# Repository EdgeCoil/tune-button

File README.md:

# Tune Button

A pocket remote for Spotify on Android. Out of the box its four keys **like** the song that's
playing, **add it to a playlist**, **skip**, and **play or pause**. Each key can also do something
else when held or double-pressed. It runs for months on a small battery and charges over USB-C.

It is **not a Bluetooth keyboard**, so nothing on the phone gets remapped. Each press sends a small,
signed Bluetooth broadcast. A companion app hears it in the background, even with the phone locked,
and does what you set that key to do.

<sub>The three four-key boards (renders of rev A, which has arrived and is being brought up): `c3-jst` with buttons on a cable, the XIAO board, and the C3 board's key side.</sub>

```
 button ──wake──► ESP32-C3 ──signed BLE broadcast──► Android app ──HTTPS──► Spotify
                 (deep sleep)                      (listens in the         like, add, skip,
                                                    background)            play/pause, …
```

> **Status: works end to end.** A one-button unit on a XIAO ESP32-C3 liked the playing song from a
> locked Samsung phone; the app heard the press in 0.8 s. The four-key firmware and app (holds,
> double presses, playback control) are written and unit-tested; on the rev A boards the C3 board's
> four keys, sleep and wake work (2026-11-05), the XIAO board is flashed (without a cell so far), and the app hasn't been
> paired with a four-key board yet. Still to do: a longer latency run on each scan mode and a
> battery-life measurement. See [`docs/design.md`](docs/design.md).

## What you need

- **The button:** one of the four-key boards (see [Hardware](#hardware)), or a hand-wired Seeed
  Studio XIAO ESP32-C3 with a small LiPo cell and one or two 12 mm tactile switches
  ([`hardware/wiring.md`](hardware/wiring.md)). There are 3D-printable cases, and layered acrylic
  cases for the four-key boards ([`hardware/case`](hardware/case/README.md)).
- **An Android phone**, version 8.0 or later.
- **Spotify Premium.** Spotify requires it on the account that owns the developer app, and the
  developer app works for up to five users.

## Set up

### 1. Create a Spotify developer app

1. Sign in at [developer.spotify.com/dashboard](https://developer.spotify.com/dashboard) and create
   an app. Tick **Web API**.
2. Add the redirect URI **`tunebutton://callback`**.
3. Copy the **Client ID**. You don't need a client secret: the app signs in with PKCE.

### 2. Flash the firmware

Pick the build for your button:

| Button | Build (`-e`) | `sh scripts/merge.sh <build>` makes |
|---|---|---|
| Hand-wired XIAO, two buttons | `xiao_esp32c3` (the default) | `tune-button-c3.bin` |
| Hand-wired XIAO, one button | `xiao_esp32c3_1btn` | `tune-button-c3-1btn.bin` |
| XIAO four-key board | `xiao_board` | `tune-button-xiao-board.bin` |
| `c3` or `c3-jst` board | `c3_board` | `tune-button-c3-board.bin` |

With PlatformIO:

```bash
cd firmware
pio test -e native            # host tests: packet encoder, signatures and key gestures
pio run -e c3_board -t upload # build and flash over USB-C
```

Or make one image (table above) and flash it at offset `0x0`, either in Chrome with
[esptool-js](https://espressif.github.io/esptool-js/) or with
`esptool.py --chip esp32c3 write_flash 0 tune-button-c3.bin`.

**Only have one button?** Wire it to D1. A press acts when you let go; holding it for 5 seconds pairs.

Things worth knowing:
- **On a computer's USB it stays awake**, so the serial port stays up: `pio device monitor` shows a
  line per wake and per key sent, and `pio run -t upload` works as is. It notices within a few ms
  when the computer goes away, and sleeps. A plain USB charger sends no USB frames, so on one it
  sleeps as usual. Build with `-DTB_USB_HEARTBEAT` to also print the raw key state once a second.
- **Otherwise the USB port vanishes while the button sleeps**, which is almost all the time. To
  flash it, plug it into a computer and press a key (it stays up once the press is sent), or hold
  **BOOT** while plugging it in.
- **If it sits in `waiting for download` after an upload**, the reset after flashing kept it in
  the bootloader: unplug and replug it. `--after watchdog_reset` (esptool) avoids this.
- **Flashing the merged image at `0x0` erases the pairing**, so pair again afterwards.
  `pio run -t upload` keeps it.
- Build options in `platformio.ini`: `TB_BURST_MS` (how long each press is broadcast) and `TB_LED_PIN`.
- **Updating from the two-button firmware** keeps the pairing (with `pio run -t upload`), and the
  app still understands a button that hasn't been updated.

### 3. Install the app

```bash
cd android
./gradlew test assembleDebug      # needs JDK 17+ and Android SDK 35
```

Install `app/build/outputs/apk/debug/app-debug.apk` on the phone, open it and work down the screen:

1. Paste the Client ID and tap **Sign in to Spotify**. (Signed in before playback control existed?
   The app asks you to sign in again, to allow it.)
2. **Pair:** hold keys 1 and 2 (top left and top right) for 3 seconds (one-button build: hold it for
   5 seconds) until the LED flickers, then tap **Pair**. Accept the Bluetooth prompt if one appears.
   Pairing makes a fresh key, so a previously paired phone stops working; a pairing that no phone
   completes changes nothing.
3. **Keys:** tap any key's press, hold or double press to choose what it does. Key 2's press needs
   a playlist.
4. Fix everything listed under *Keep listening in the background*. **On Samsung phones, also add the
   app to *Never sleeping apps*,** or presses stop being heard after a few days.
5. Tap **Test without the device** to check the Spotify side on its own.

## Using it

Press a key. Within a moment the phone buzzes once and shows a notification, for example
"♥ Liked — Title · Artist" or "⏭ Next track". If something goes wrong it buzzes twice and says why:
nothing playing, signed out, a local file, and so on. Podcast episodes work too.

What a key can do, on press, hold (0.6 s) or double press:

| | |
|---|---|
| **The song** | like it, remove it from Liked Songs, add it to a playlist, remove it from a playlist |
| **Playback** | play / pause, next, previous, volume up or down 10 %, shuffle on / off, repeat (off → all → one), play a playlist |
| **Anything else** | call a webhook, such as a Home Assistant automation. It gets the key, the gesture and the song |

Each slot has its own playlist, so key 2 could add to one playlist and key 2 held to another.

**Holds and double presses cost a little speed, on that key only.** A key with nothing on hold or
double press sends the moment it goes down. One with a hold action waits for you to let go (or for
the hold); one with a double press waits 0.3 s for a second press. The button has to know which keys
wait, so after changing those, the app asks you to hold keys 1 and 2 for 3 seconds and tap **Send
key settings**. That doesn't re-pair anything.

Quick presses all count: three fast presses of skip are three skips.

The app's *Recent presses* list shows, for each press, how long the phone took to hear it, how long
Spotify took, the button's battery level and the result.

## Hardware

| Option | What it is | State |
|---|---|---|
| **Hand-wired XIAO** | A XIAO ESP32-C3 with one or two switches and a LiPo: [`hardware/wiring.md`](hardware/wiring.md) | One-button unit built and working |
| **3D-printed case** | Parametric OpenSCAD, with ready STLs: [`hardware/case/`](hardware/case/) | Ready to print |
| **Four-key PCBs** | Three boards: one carrying a XIAO, one with the ESP32-C3 module on board, and a small one that takes buttons on a cable. [`hardware/pcb/`](hardware/pcb/) | Rev A in bring-up; XIAO rev B designed |

The firmware supports all four boards. It runs on the rev A C3 board and is flashed on the rev A XIAO board (without a cell so far); `c3-jst` is untested.

## How it's put together

| Path | What it is |
|---|---|
| [`firmware/`](firmware/) | PlatformIO / Arduino firmware for the ESP32-C3 (NimBLE) |
| [`android/`](android/) | The companion app (Kotlin, Android 8+) |
| [`protocol/`](protocol/) | The broadcast format, and `gen_vectors.py`, which makes the test vectors both sides check against |
| [`hardware/`](hardware/) | Wiring, parts, the case and the PCBs |
| [`docs/design.md`](docs/design.md) | How it works, security, power budget, latency and bench tests |

Each press is signed with a key shared at pairing and carries a counter, so the app ignores copies
and anything not from your button. [`docs/design.md`](docs/design.md) has the details.

## Licence

| What | Licence |
|---|---|
| The case and PCBs: `hardware/case/`, `hardware/pcb/` (OpenSCAD and KiCad sources, STLs) | [CERN-OHL-S-2.0](LICENSES/CERN-OHL-S-2.0.txt) |
| Firmware, app, protocol tools | [MIT](LICENSES/MIT.txt) |
| The Gradle wrapper (`android/gradlew*`, `android/gradle/wrapper/`), as shipped by Gradle | [Apache-2.0](LICENSES/Apache-2.0.txt) |
| Documentation (`README.md`, `docs/` including the renders, `hardware/wiring.md`, `protocol/spec.md`) | [CC BY 4.0](LICENSES/CC-BY-4.0.txt) |
| The EdgeCoil mark (`hardware/pcb/edgecoil-mark.svg` and the silkscreen drawn from it), name and URL | [All rights reserved](LICENSES/LicenseRef-EdgeCoil-Mark.txt) |

Each source file carries an SPDX header, and [`REUSE.toml`](REUSE.toml) covers the rest by path.

The board licence does not cover the EdgeCoil mark, name or URL on the silkscreen. If you make or
sell boards from these designs, take them off.

Spotify is a trademark of Spotify AB. This project is not affiliated with or endorsed by Spotify.

---

edgecoil · [edgecoil.dev](https://edgecoil.dev)

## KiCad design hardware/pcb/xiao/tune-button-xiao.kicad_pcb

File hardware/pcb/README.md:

# Four-key PCBs

Three circuit boards for a four-key Tune Button:

- **`xiao/`**: a Seeed XIAO ESP32-C3 plugged into sockets, with four Cherry MX switches.
- **`c3/`**: the ESP32-C3 module, USB-C, charger and regulator on the board itself, with four MX
  switches on the back.
- **`c3-jst/`**: the same circuit as `c3/` on a much smaller board, with the buttons on wires to a
  7-pin JST connector instead of switches on the board.

The MX boards put their switches in a 2 × 2 grid at the standard 19.05 mm keyboard pitch.

| `xiao/` | `c3/` (key side) | `c3/` (parts side) | `c3-jst/` |
|---|---|---|---|
|  |  |  |  |

<sub>Rendered from the design files with KiCad. The connectors, switches and keycaps are simplified
stand-ins. The XIAO render is rev A (USB at the top edge, wired BAT header); rev B is described
under [`xiao/` rev B](#xiao-rev-b).</sub>

> **Status: rev A (tag `rev-a`, ordered 2026-10-25 on one JLC panel) has arrived and is being
> brought up.** The C3 board runs the four-key firmware (2026-11-05: all four keys, sleep and wake;
> see [Firmware](#firmware)); the XIAO board is flashed without a cell, its keys not yet confirmed,
> and the with-cell flash check (below, D0) is still to do; `c3-jst` is untested. Every board
> passes KiCad's electrical and design rules checks, with nothing unconnected and the board
> matching its schematic.
>
> **`xiao/` is now rev B: reviewed, not yet ordered** (rev A is the tag). Thirteen DFM audit
> rounds; the last, at d1087fc, was clean. The XIAO is turned so its USB-C faces the left edge, a
> spring pin under it meets its BAT+ pad in place of rev A's wired header, and each switch
> footprint takes a switch on either side of the board. **Before ordering, three checks on a rev A
> XIAO board:** the gap from the board to a plugged-in XIAO's underside (11.0 mm assumed), the BAT+
> pad's position, and a USB flash with a cell connected (D0). See [`xiao/` rev B](#xiao-rev-b).

## The three boards at a glance

| | `xiao/` | `c3/` | `c3-jst/` |
|---|---|---|---|
| Size | 46 × 68.5 mm (rev A: 67) | 46 × 69.7 mm | 36 × 50 mm |
| Brain | XIAO ESP32-C3 on two 1 × 7 sockets | ESP32-C3-WROOM-02 module; its antenna sits over a notch in the top-left corner | The same module; its antenna overhangs the top edge |
| Keys | 4 MX, on either side of the board | 4 MX on the back | A 7-pin JST-PH (J3) for your own buttons |
| USB-C, charger, 3.3 V | On the XIAO | On the board: TP4054 charger (≈ 200 mA), load sharing, RT9080 regulator (600 mA, about 2 µA when idle) | As `c3/` |
| USB-C position | On the XIAO, left edge (rev A: top) | Centre of the bottom edge | Bottom edge, left |
| Battery | JST-PH socket, right edge; a spring pin up to the XIAO's BAT+ pad (BAT− returns through the socket) | JST-PH socket | JST-PH socket (J2), right edge |
| Which side is which | Everything on top; the switches on top or the back | Keys, LEDs, logo and name on the back (the key side); all the electronics on the front, facing into the case | Every part on the front; logo, name and the J3 pin list on the back |
| Mounting | 4 × M2 | 4 × M2 | 2 × M2 (see [Mounting](#mounting)) |
| Soldered by you | The MX switches, and the XIAO's header pins unless it came pre-soldered (J4's height assumes a standard 2.5 mm spacer) | The MX switches and 2 LEDs on the back | Nothing (JLC fits every part) |

### `c3-jst`'s button connector (J3)

JST-PH, 2 mm pitch. Each button goes between its K pin and GND.

| Pin | 1 | 2 | 3 | 4 | 5 | 6 | 7 |
|---|---|---|---|---|---|---|---|
| Signal | GND | K1 | K2 | K3 | K4 | LED | 3V3 |

- **LED (pin 6)** goes through a 330 Ω resistor: about 4 mA into a red LED, enough for a lit button.
  It is the one pin without an ESD clamp, guarded only by R15 and the chip's own protection.
- **3V3 (pin 7)** is the regulator's output, shared with the module's 350 mA Wi-Fi bursts. Keep
  what you hang on it under about 100 mA.
- The key lines have their own ESD array (U5), since they run out on wires to buttons people touch.

## When the boards arrive

- **On the XIAO board, connect a cell and check the XIAO still flashes over USB.** D0 is a
  strapping pin and the battery divider holds it mid-rail (see the pin map); rev A was only flashed
  without a cell. If it fails, rev B moves the divider before it's ordered.
- **On `c3-jst`, check R16 and C8 are fitted** (top right, beside the regulator). They damp the
  ringing when USB is plugged in: without them a long cable can push the regulator's input to
  about 6.6 V, past its 6.5 V limit.
- **Cut `c3-jst`'s two right-edge panel tabs with flush cutters; don't snap them.** They sit close
  to the connectors' anchor pads. File the remnants flush.
- **Check the battery plug before connecting a cell.** Pin 1 (marked **+**) is the positive side,
  but JST-PH LiPo leads aren't wired consistently between sellers, and nothing on the boards
  protects against a reversed cell.
- **With USB in and no cell,** 3V3 should read 3.3 V before anything else is connected.

## Ordering

**For a few boards, order the one you want on its own, with Economic assembly** (see *Ordering one
board on its own* below). Economic has lower set-up and stencil fees, and Basic and Preferred parts
carry no per-type fee there.

Rev A was ordered as one panel with JLC's Standard assembly, because Standard needs at least
70 × 70 mm, which no single board is. That rested on an assumption nobody checked: that the ESP32
module needs Standard. The Wiegand Bridge's ESP32-S3 module was refused Economic, but JLC has
offered Economic for two later boards with this same ESP32-C3-WROOM-02, and it was never tried for
these. The panel is still the way to get all three designs in one order, or many of one. Whether
Economic accepts a customer panel of several designs is untested.

For the panel: run `./build.sh`, then `python3 panel.py` (see [Rebuilding](#rebuilding)), and
upload from `panel/fab/`.

**PCB options**
- Upload `tune-button-panel-gerbers.zip`. It should read about 148 × 87 mm, 2 layers.
- Different designs **3**, delivery format **Panel by customer**.
- 1.6 mm, **black** mask, white legend, **lead-free HASL**.
- Min via hole **0.3mm/(0.4/0.45mm)**, the standard option. No hole is under 0.3 mm, and the
  0.2 mm option took the quote from $20 to $70.
- Mark on PCB: **Remove Mark**. The boards carry no order-number marker.

**Assembly**
- **Standard**, **top side only**. Upload `tune-button-panel-jlc-bom.csv` and
  `tune-button-panel-jlc-cpl.csv`.
- Add a remark: *"Customer panel of 3 designs. The modules' antennas and the USB-C sockets overhang
  their board edges by design."*
- Each part is prefixed with its board (`XIAO_`, `C3_`, `JST_`).
- **Check the placement preview before paying.** `edgecoil_pcb.jlc` (in `vendor/`) already corrects
  every rotation where JLC's footprint differs from KiCad's, each checked pad by pad against JLC's
  own footprint by `edgecoil_pcb.jlc_verify` (RT9080, AO3401A, SRV05-4, TP4054, USB-C, the 7-pin
  JST, the XIAO board's sockets, rev A's header and rev B's spring pin), but a wrong SRV05-4
  rotation (U2, and U5 on `c3-jst`) would short the 3V3 rail.

**What JLC fits and what's left for you**
- JLC fits everything on the front of each board, including the XIAO board's sockets (and rev A's
  2-pin header; rev B's spring pin is SMD). Those are through-hole, at a hand-soldering fee of about
  $3.50 plus a per-joint rate.
- Left for you: the MX switches, the C3 board's two back LEDs and its UART header, the XIAO itself,
  the batteries and the buttons.

**Part costs.** Parts are chosen to keep JLC's per-type fee down:
- **Basic or Preferred, no fee:** every passive, the LEDs, the MOSFET, the diodes, the tact
  switches, the TP4054 charger and the SRV05-4 ESD part.
- **Extended, one fee per type:** seven types, namely the ESP32-C3 module, the USB-C socket, the
  battery JST, the RT9080 regulator, `c3-jst`'s 7-pin JST, and the XIAO board's sockets (C2932672,
  8.5 mm tall) and, on rev A, its header (C492401); rev B has the spring pin (C5221289) instead.

Catalogue status changes, and the build doesn't check it.

JLC's online DFM check reports a few "danger" items that are fine:
- the USB-C shell slots at 0.6 mm, the connector's own size;
- a via-to-hole spacing rule that applies only to filled vias (these are tented);
- a solder-mask opening near copper on the same net as its pad.

<details>
<summary>Ordering one board on its own</summary>

Upload `<board>/fab/tune-button-<board>-gerbers.zip` with the same board options as above. For
assembly, add `-jlc-bom.csv` and `-jlc-cpl.csv`, top side only. Black mask and lead-free HASL are
available with Economic assembly for 2–50 boards; ENIG would force green.

The boards are under Standard's 70 × 70 mm minimum, so order Economic. Their USB-C, battery
socket and module sit closer to the edges than JLC's 2.5 mm assembly rule, so if JLC asks for rails:
- have them on the **left and right edges only**, since the USB-C overhangs the bottom edge and
  the antenna overhangs the top;
- ask for **mouse bites, not V-cut.** The ground pour runs 0.3 mm from the edges, which meets JLC's
  routed-edge rule but not its 0.4 mm V-cut one.

On `c3-jst`, add a remark placing the tabs:
- left edge: only between 14 and 25 mm from the top (below that are a mounting hole, a VBUS track
  0.7 mm in, and C1, a capacitor that cracks if the board flexes next to it);
- right edge: only between 25 and 28.5 mm or 39.5 and 44.5 mm (higher up is C8, another such
  capacitor, and the ends keep the bites 1.5 mm from J2's and J3's pads).

Both right-edge windows are within 2 mm of J2's and J3's anchor pads, so cut tabs there rather
than snapping them.

</details>

<details>
<summary>How the panel is laid out</summary>

- **Frame:** the boards sit side by side (XIAO, C3, `c3-jst`) in a 6 mm frame. It has rails on the
  left and right and bars across the top and bottom. The bars stay at least 2.5 mm from every board
  edge and 1.5 mm from anything that overhangs one. The frame carries JLC's 1.152 mm tooling holes
  in its four corners and three fiducials 4.35 mm in from the rails' outer edges. JLC's capabilities
  page now asks for 5 mm tooling edges, 2 mm tooling holes and 1 mm fiducials 3.85 mm from the
  edges, and mouse-bite tabs at least 5 mm wide (these are 2.3–3.0 mm); rev A's panel was accepted
  with this frame, but check the current note before a panel order.
- **Where tabs may go:** mouse-bite tabs join the boards to each other and to the frame. They go
  only where:
  - no track, via or pad comes within 1 mm of the edge;
  - they are at least 2 mm from a mounting hole;
  - nothing overhangs the edge.
- **Distances `panel.py` enforces, and stops if broken:**
  - no tab within 3 mm of an 0805 or larger ceramic capacitor, which can crack when the board
    flexes;
  - no bite within 1.5 mm of any pad (JLC's mouse-bite rule).
- **Tab shape:** each tab is 3 mm wide (2.3–2.9 mm on `c3-jst`) with 1 mm fillets, so it is about
  5 mm wide where it meets the board. That matches JLC's 5 mm figure if its review asks. The bites
  are 0.5 mm holes at about 0.8 mm pitch (0.86–0.96 mm on the two cut tabs), set 0.25 mm inside the
  board. The ground pour is held back around each tab, and `panel.py` checks each board is joined to
  the panel only at its tabs.
- **`c3-jst`'s five tabs:** one on its left (shared with the C3), two to the right rail, one to the
  top bar and one to the bottom bar. JLC wants tabs 2 mm from connector pads. The two right-edge
  tabs can't manage that, and end about 1.8 mm from the battery socket's anchor pads (the lower one
  also from J3's). So their bites sit outside the board edge instead, and they are the two to cut
  rather than snap.
- **Building it:** `panel.py` uses [KiKit](https://github.com/yaqwsx/KiKit) 1.8.1 and relies on its
  internals (such as how it spaces the bites). Install it where Python can also see KiCad's
  `pcbnew`, for example in a venv made with `--system-site-packages`, then `pip install
  kikit==1.8.1`.

</details>

## Pin map

| Signal | XIAO board | C3 boards | Notes |
|---|---|---|---|
| K1 (top left) | D1 / GPIO3 | GPIO3 | Same pin as the hand-wired like button |
| K2 (top right) | D2 / GPIO4 | GPIO4 | Same pin as the hand-wired playlist button |
| K3 (bottom left) | D3 / GPIO5 | GPIO5 | |
| K4 (bottom right) | D4 / GPIO6, and through D1 (1N4148WS) onto GPIO5 | GPIO0 | See below |
| Battery divider (2 × 220 kΩ) | D0 / GPIO2 | GPIO1 | ADC1 |
| LED (1 kΩ) | D5 / GPIO7 | GPIO10 | |
| USB D− / D+ | (XIAO) | GPIO18 / GPIO19 | Native USB, also used for flashing |
| Straps | (XIAO) | GPIO2 and GPIO8 pulled up 10 kΩ; GPIO9 to BOOT | |

Every key switches to ground and uses the chip's internal pull-up.

**The XIAO board's K4 is a compromise.**
- **Why:** the C3 can only wake from deep sleep on GPIO0–5, and the XIAO brings out just GPIO2–5 of
  those. GPIO2 is taken by the battery reading, which has to be on ADC1 (GPIO0–4).
- **D0 (GPIO2) is a strapping pin, and the divider holds it at about half the cell's voltage**
  (1.5–2.1 V for a 3.0–4.2 V cell), between the C3's low and high thresholds. Espressif says GPIO2
  doesn't choose the boot mode but recommends pulling it up against glitches, and one Seeed forum
  user couldn't flash a XIAO until a divider like this was removed. **Untested here:** with a cell
  connected, check that the XIAO still flashes over USB. If it doesn't, unplug the cell (or flash
  the XIAO out of its sockets), and rev B moves the divider to D2 (and K2 to D0, with a pull-up)
  before it's ordered.
- **How it works:** K4 is read on D4, and also pulls K3's line low through a diode. That diode must
  be a 1N4148WS rated at most 0.715 V at 1 mA (C2128 is). A Schottky leaks enough when warm to drag
  D4 low while K3 is held.
- **Telling them apart:**
  - a K4 press wakes the chip on GPIO5 with D4 low;
  - a K3 press wakes it on GPIO5 with D4 high.
- **The catch:** a very quick tap on K4 could be released before the firmware reads D4, and would
  then read as K3. The firmware's deep-sleep wake stub reads D4 within about a millisecond of
  waking, far shorter than any tap, so this is handled.

The C3 boards have GPIO0 and GPIO1 free, so all four keys are direct wake pins there.

## Things to know

- **Regulator (C3 boards).** The RT9080 is rated at 600 mA (current limit at least 610 mA) and draws
  about 2 µA when idle, which matters most for something that sleeps for months.
  - **Supply:** Espressif asks for at least 500 mA, because Wi-Fi transmit peaks reach about 350 mA.
    With 0.31 V of dropout at 600 mA (about 0.2 V at 350 mA), the rail holds 3.3 V through those
    peaks down to a cell of about 3.5 V.
  - **Input limit:** 5.5 V (6.5 V absolute), which is why C1 has a 1 Ω damping resistor against
    plug-in ringing. On `c3-jst`, C1 sits by the USB-C, at the far end of the supply path from the
    regulator (VBUS, then D2, then VSYS). So R16 and C8 (1 Ω in series with 10 µF) damp it again
    beside the regulator.
  - **Alternative:** the MCP1700 (250 mA, 1.6 µA) is a lower-current part in a SOT-23 footprint,
    not a drop-in.
- **Low battery.** Below about 3.6 V, a Wi-Fi-sized burst sags the C3's 3.3 V rail under 3.0 V
  (simulated with the routed copper). On `c3-jst` the threshold depends on the load on J3:
  - 3.55 V with nothing on J3;
  - 3.6 V with 50 mA;
  - 3.7 V with 100 mA.

  The firmware should stop using radio-heavy features below these.
- **Use cells with a protection board.** D4, a Schottky across the battery FET, keeps the supply up
  for the few milliseconds after USB is unplugged. While on USB, though, its leakage trickles into
  the cell: negligible at room temperature, about +15 µA at 60 °C. Once charging finishes, only the
  cell's own protection board stops a hot, permanently plugged-in board slowly overcharging it.
  Ordinary LiPo cells with a PCM are fine.
- **MX switches** use the 5-pin PCB-mount footprint, which also takes 3-pin plate-mount switches.
  The boards aren't hot-swap. On the C3 board they mount on the back and are soldered from the
  front, where their leads come through between the parts; trim the leads short.
- **Case clearance (C3 board).** The front faces the case floor. The tallest parts there are the
  JST socket (5.5 mm) and the module and USB-C (about 3.3 mm), so allow that much under the board,
  plus the battery. RESET and BOOT are on that side, reachable with the case open. `c3-jst` has
  nothing on its back, so it can sit either way up.
- **`c3-jst` debug UART.** TP1 (TX) and TP2 (RX) are bare pads; take ground from J3 pin 1 or the
  USB-C shell.
- **XIAO header spacing.** The two rows are 15.24 mm (0.6″) apart, centre to centre, as in Seeed's
  own KiCad footprints (OPL_Kicad_Library, `XIAO-ESP32-C3-DIP`). Still, measure your XIAO across
  its two rows of pins.
- **Rev B.** With C1 at the low end of Samsung's DC-bias data (3.74 µF at 5–5.5 V), the C3 board's
  regulator input reaches 6.28 V when plugged in, against its 6.5 V limit. That's the worst case: a
  stiff 5.5 V source, a thick 2 m cable and a full cell, simulated with the routed copper.
  `c3-jst` reaches 5.98 V. Across 150 Monte Carlo runs the C3's worst is 6.27 V, none over the
  limit, so rev A is fine. For rev B, either use a C1 that keeps at least 6 µF at 5.5 V (about
  5.9 V worst; for example a 10 µF 1206 or 22 µF 0805, 25 V), or copy `c3-jst`'s fix: C1 by the
  USB-C and an RC damper at the regulator.

### Mounting

- **`xiao/`:** the four M2 holes are all clear of the keycaps.
- **`c3/`:** the four M2 holes are clear of the keycaps. Use nylon washers or standoffs: tracks run
  within 2 mm of H3 (left edge, 23 mm down), where a metal screw head could wear through the mask.
- **`c3-jst/`**, two M2 holes:
  - **H2:** use a nylon screw, or nylon washers on both faces. K1 (front) and K3 (back) run within
    1.7 mm of its centre, and VBUS (back) at 2.4 mm, under any metal head or nut.
  - **H1:** only the ground pour is under its head; the nearest track or via is 2.5 mm out.
  - **Support:** support the board behind J2 and J3 in the case, since the holes are 10–15 mm from
    where the plugs push.

### `xiao/` rev B

- **Why:** on rev A the XIAO's antenna lead and the wires from J4 to its BAT pads crossed the
  switches. On rev B the XIAO's far end (away from its USB-C, where the U.FL antenna plug is, which
  on rev A pointed at the keys) faces the top right of the board, where only J3, the LED and its
  resistor, and H2's screw are (no switches). Mount the FPC antenna in the case, off the board: both
  copper layers are ground pour, which would detune it stuck flat on the board.
- **The XIAO** is turned 90° anticlockwise (as you look at the front), so its USB-C faces the left
  edge. J1 (D0–D6) is the lower socket and J2 the upper, both reading left to right from the USB
  end. The battery JST (J3) moved to the right edge. The board is 1.5 mm taller.
- **A spring pin, J4,** stands under the XIAO and presses on its BAT+ pad, so there are no wires to
  solder. It is a YIYUAN YTC1P-8535-01 (C5221289): 12 mm free, 11 mm at working height, 100 g. The
  battery's negative returns through the socket: the XIAO's BAT− pad is its GND, which J2 pin 2
  carries. A first layout had a second pin on BAT−, but the two pads are 1.905 mm apart, closer than
  the pins' 2.0 mm flanges, so the second pin had to be staggered, which still left VBAT and GND
  metal 0.2 mm apart.
- **Unplug the cell before taking the XIAO out:** with it connected, J4 is a bare 12 mm post at the
  cell's voltage.
- **Check two things on a real XIAO before ordering.** The pad positions come from Seeed's KiCad
  footprint (OPL_Kicad_Library, `XIAO-ESP32-C3-SMD`), not a measured part: BAT+ about 3.2 mm in from
  the D0–D6 row and 7.2 mm along it from the D0 pin (level with D3), BAT− nearer the USB end. And
  the 11 mm working height assumes the 8.5 mm socket plus a 2.5 mm header spacer: measure from the
  board to the underside of a plugged-in XIAO. Seeed's photo of the XIAO's back shows the BAT+ pad
  itself as about 1.9 × 0.9 mm (the footprint's land is 2.5 × 1.1), so J4's 0.9 mm tip has roughly
  ±0.45 mm along the row to stay on it, against the socket's play, JLC's placement and the 12 mm
  pin's lean (1° moves the tip 0.19 mm). A miss is harmless (BAT− is 1.45 mm away), but on arrival
  check that J4 stands upright, and mark its tip (a dab of marker) to see where it lands on the
  XIAO. The same series comes in 10.5 mm (YTC1P-8530, C5221283) and 11.5 mm.
- **Reversible switches.** Each switch footprint (`lib/tune-button.pretty`) has both pin pairs: a
  switch on the front uses one pair, a switch on the back the mirrored pair, and the centre and
  side posts serve both. Pads are 2.0 mm (KiCad's are 2.2), leaving 0.84 mm between a front pin 1
  and a back pin 2, which are different nets. The firmware is unchanged: K1 is top left as seen
  from the front, so with the switches on the back K1 is top right as you look at the keys.
- **With the switches on the back, the LED (D2) faces into the case,** like everything else on the
  front. It's visible only with front-mounted switches, or through a light path in the case.

## Firmware

Build `xiao_board` for the XIAO board and `c3_board` for `c3` and `c3-jst` (see the top-level
README). `c3_board` has run on a rev A C3 board (2026-11-05: all four keys, sleep and wake on USB
and battery); `xiao_board` is flashed on a rev A XIAO board (without a cell), but its keys aren't
confirmed yet. On the XIAO board, a deep-sleep wake stub reads D4 within about a millisecond of
waking, so even a very quick tap on K4 reads as K4.

## Rebuilding

Everything is generated. Edit the scripts and rebuild; don't edit the KiCad files, because a rebuild
overwrites them.

1. **[`gen.py`](gen.py)** holds the parts, nets and placement for all three boards. It writes the
   schematic, with a label on every pin, and an unrouted board from the same netlist, through the
   shared pipeline, [EdgeCoil/edgecoil-pcb](https://github.com/EdgeCoil/edgecoil-pcb), vendored in
   [`vendor/`](vendor/).
2. **[`route.py`](route.py)** lays the copper and fills the pours.
   - **Frozen routing:** each board's `routing.json` holds its reviewed tracks and vias, and
     `route.py` replays them. A fix is then a small edit to that file, not a new layout.
   - **`route.py --reroute <board>`:** autoroutes afresh with Freerouting, adds ground stitching
     vias and retries until KiCad's DRC is clean. Then **`route.py --freeze <board>`** records it.
   - **Fresh review needed:** a reroute changes the whole layout. So does moving a part in
     `gen.py`, since the frozen copper then no longer meets its pads (DRC catches that).
3. **[`build.sh`](build.sh)** runs both, then ERC and DRC with the schematic parity check. It
   exports gerbers, drill files, BOM, pick-and-place, a schematic PDF and renders into
   `<board>/fab/`.
4. **[`panel.py`](panel.py)** builds the three-board panel into `panel/`.

```sh
KICAD_SYMBOL_DIR=/path/to/kicad/symbols FREEROUTING=/path/to/freerouting-2.1.0.jar ./build.sh
python3 panel.py          # with KiKit 1.8.1, see "How the panel is laid out"
```

It needs KiCad 9, Java 21 and Freerouting 2.1.0 (later Freerouting releases need Java 25). To
hand-route instead, stop after `gen.py` and open the project in KiCad.

## Licence

The EdgeCoil mark, name and URL on the back silkscreen are not covered by the board licence (see
[`LICENSES/LicenseRef-EdgeCoil-Mark.txt`](../../LICENSES/LicenseRef-EdgeCoil-Mark.txt)). To build
boards to share or sell, remove the `logo` and the `edgecoil.dev` text from `gen.py` and rebuild.

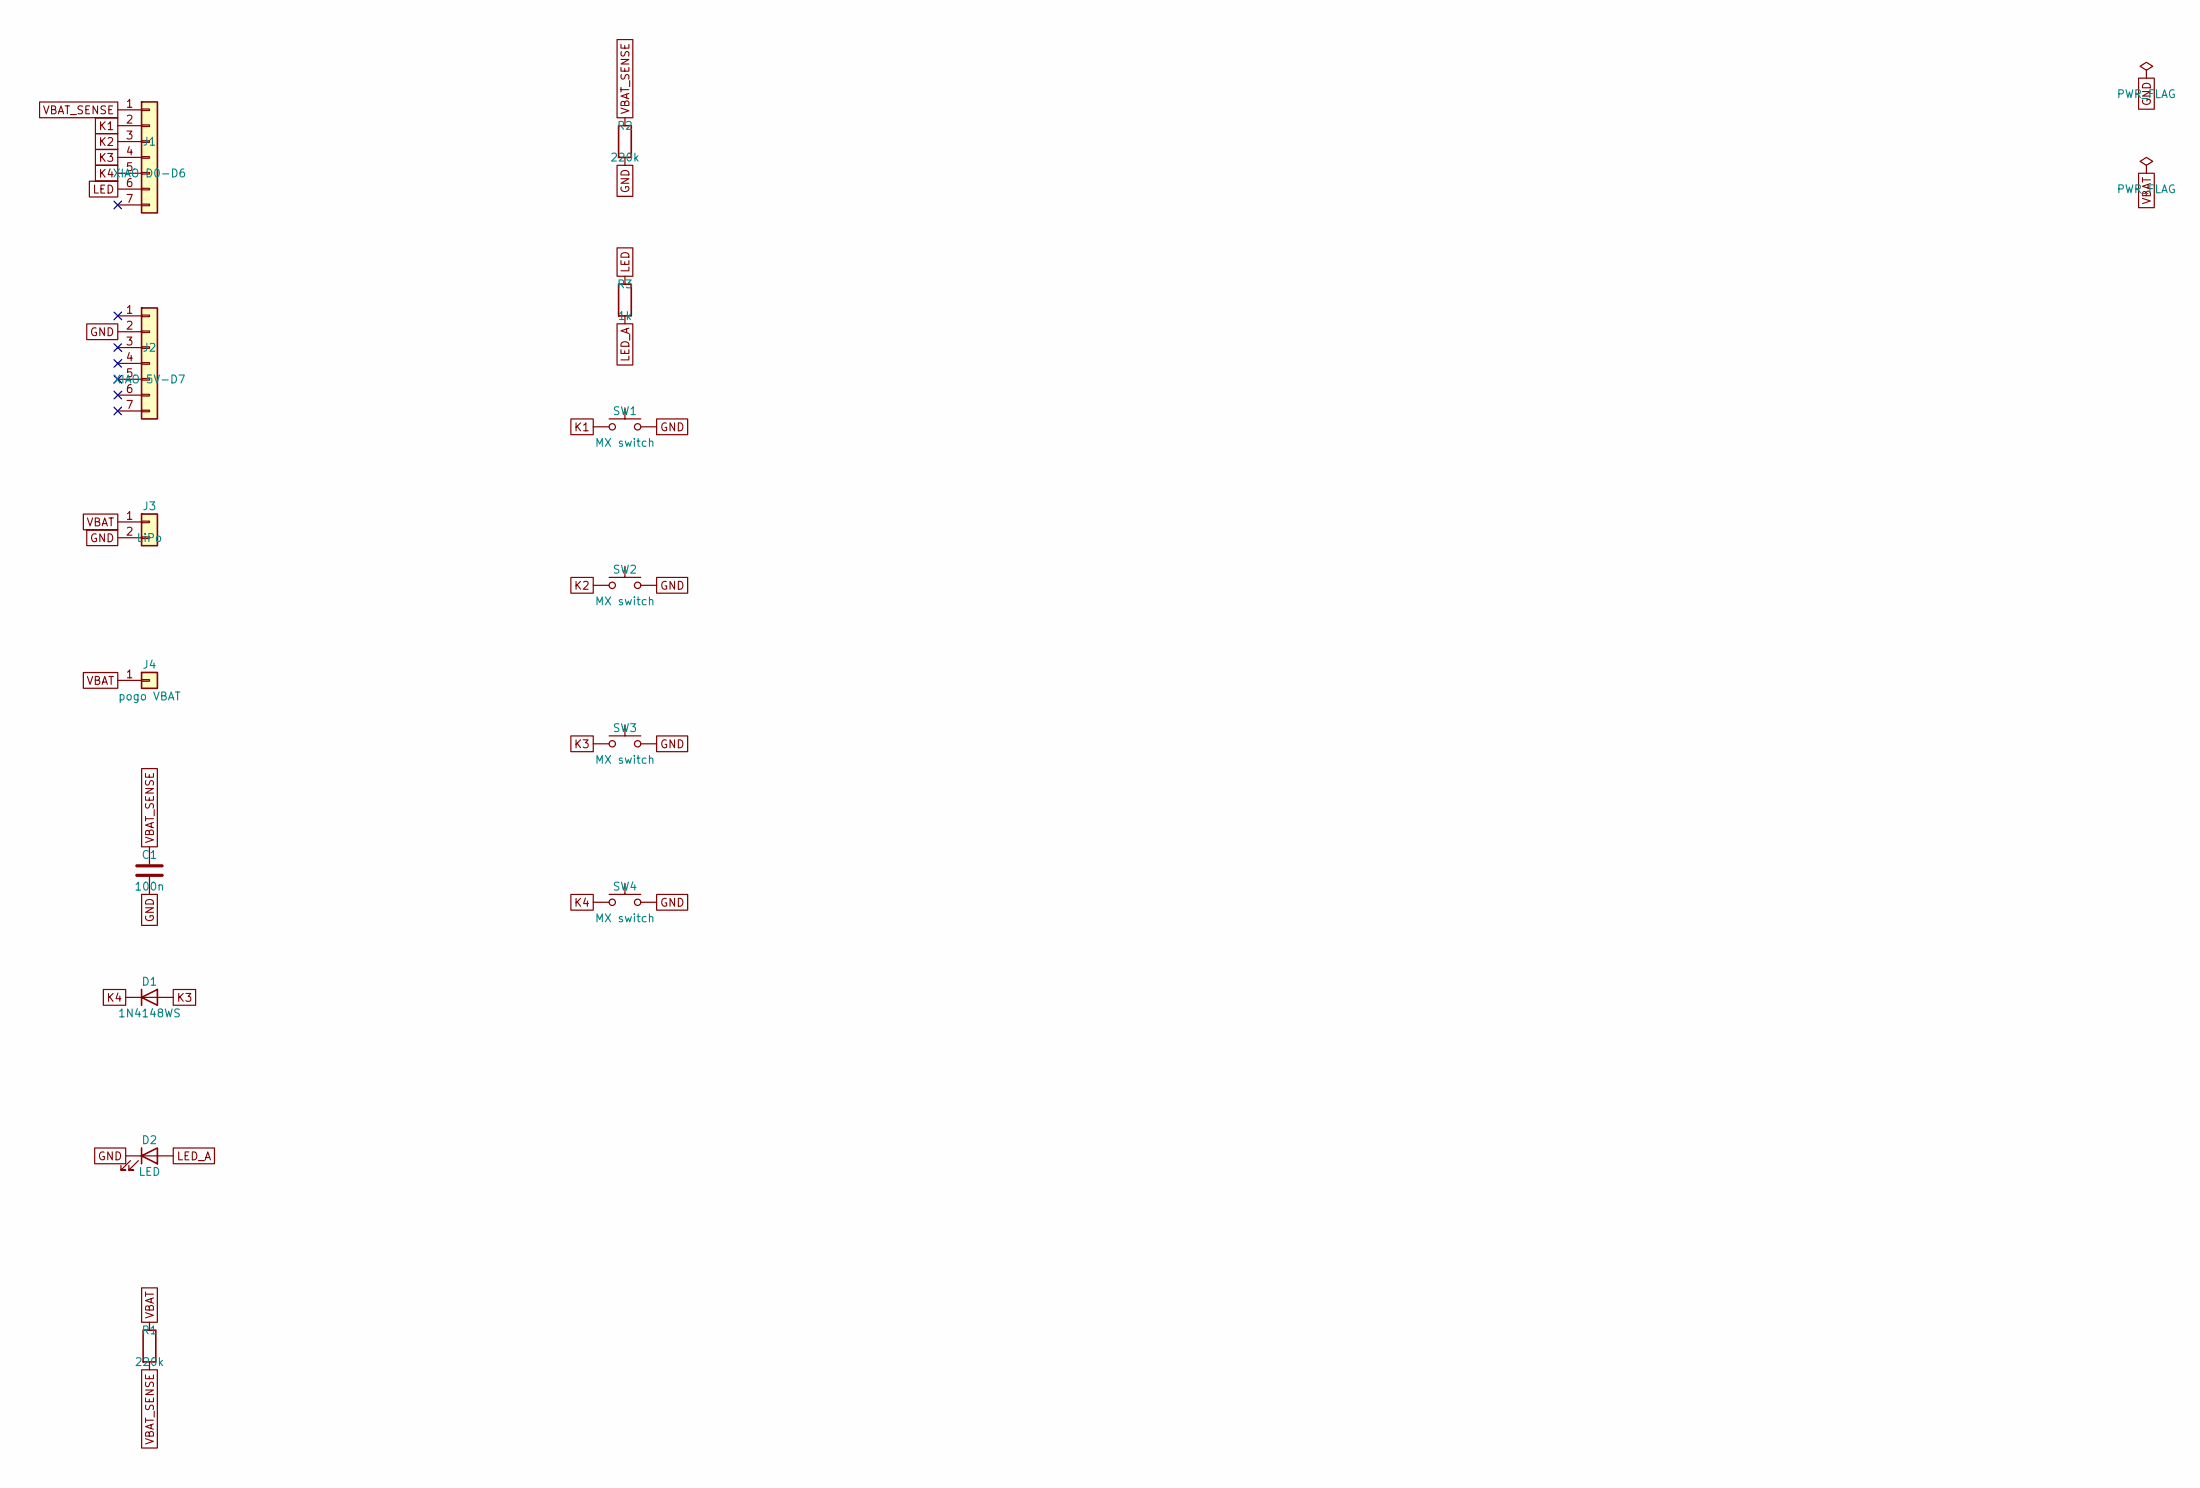
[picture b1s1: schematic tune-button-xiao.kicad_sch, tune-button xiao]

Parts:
C1: 100n; C_0603_1608Metric; LCSC C14663
D1: 1N4148WS; D_SOD-323_HandSoldering; MPN 1N4148WS; LCSC C2128
D2: LED; LED_0603_1608Metric; LCSC C2286
J1: XIAO D0-D6; PinSocket_1x07_P2.54mm_Vertical; MPN Kinghelm KH-2.54FH-1X7P-H8.5; LCSC C2932672
J2: XIAO 5V-D7; PinSocket_1x07_P2.54mm_Vertical; MPN Kinghelm KH-2.54FH-1X7P-H8.5; LCSC C2932672
J3: LiPo; JST_PH_S2B-PH-SM4-TB_1x02-1MP_P2.00mm_Horizontal; MPN JST S2B-PH-SM4-TB; LCSC C295747
J4: pogo VBAT; PogoPin_YTC1P_D2.0_SMD; MPN YIYUAN YTC1P-8535-01; LCSC C5221289
R1, R2: 220k; R_0603_1608Metric; LCSC C22961
R3: 1k; R_0603_1608Metric; LCSC C21190
SW1, SW2, SW3, SW4: MX switch; SW_Cherry_MX_1.00u_PCB_Reversible; MPN Cherry MX (3 or 5 pin)

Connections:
GND: C1.2, D2.1 (K), J2.2, J3.2, R2.2, SW1.2, SW2.2, SW3.2, SW4.2
K1: J1.2, SW1.1
K2: J1.3, SW2.1
K3: D1.2 (A), J1.4, SW3.1
K4: D1.1 (K), J1.5, SW4.1
LED: J1.6, R3.1
LED_A: D2.2 (A), R3.2
VBAT: J3.1, J4.1, R1.1
VBAT_SENSE: C1.1, J1.1, R1.2, R2.1

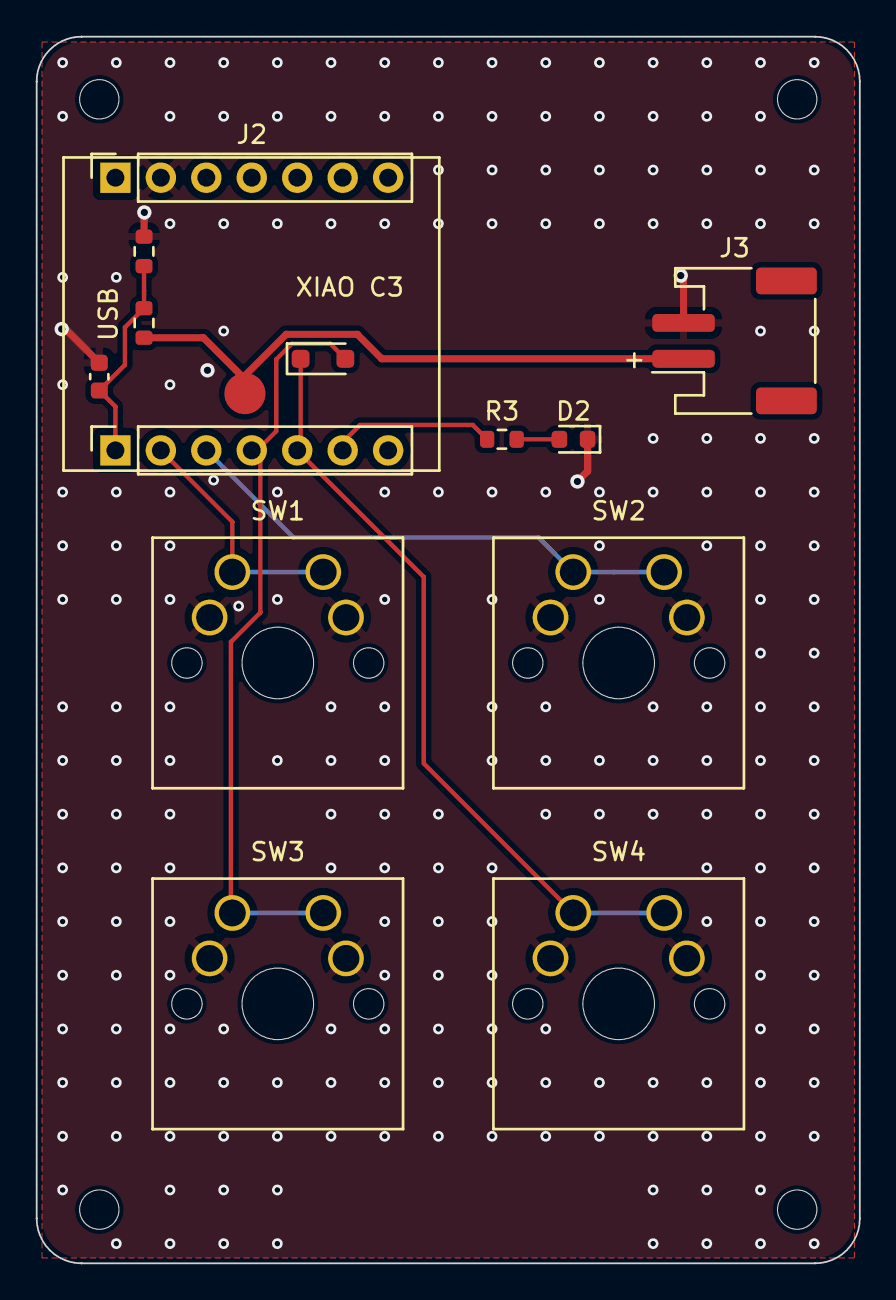
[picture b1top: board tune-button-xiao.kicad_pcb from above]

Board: 2 copper layers, 46.0 x 68.5 mm, 18 parts (0 on the bottom side), 9 nets.

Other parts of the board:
H1, H2, H3, H4: M2; MountingHole_2.2mm_M2

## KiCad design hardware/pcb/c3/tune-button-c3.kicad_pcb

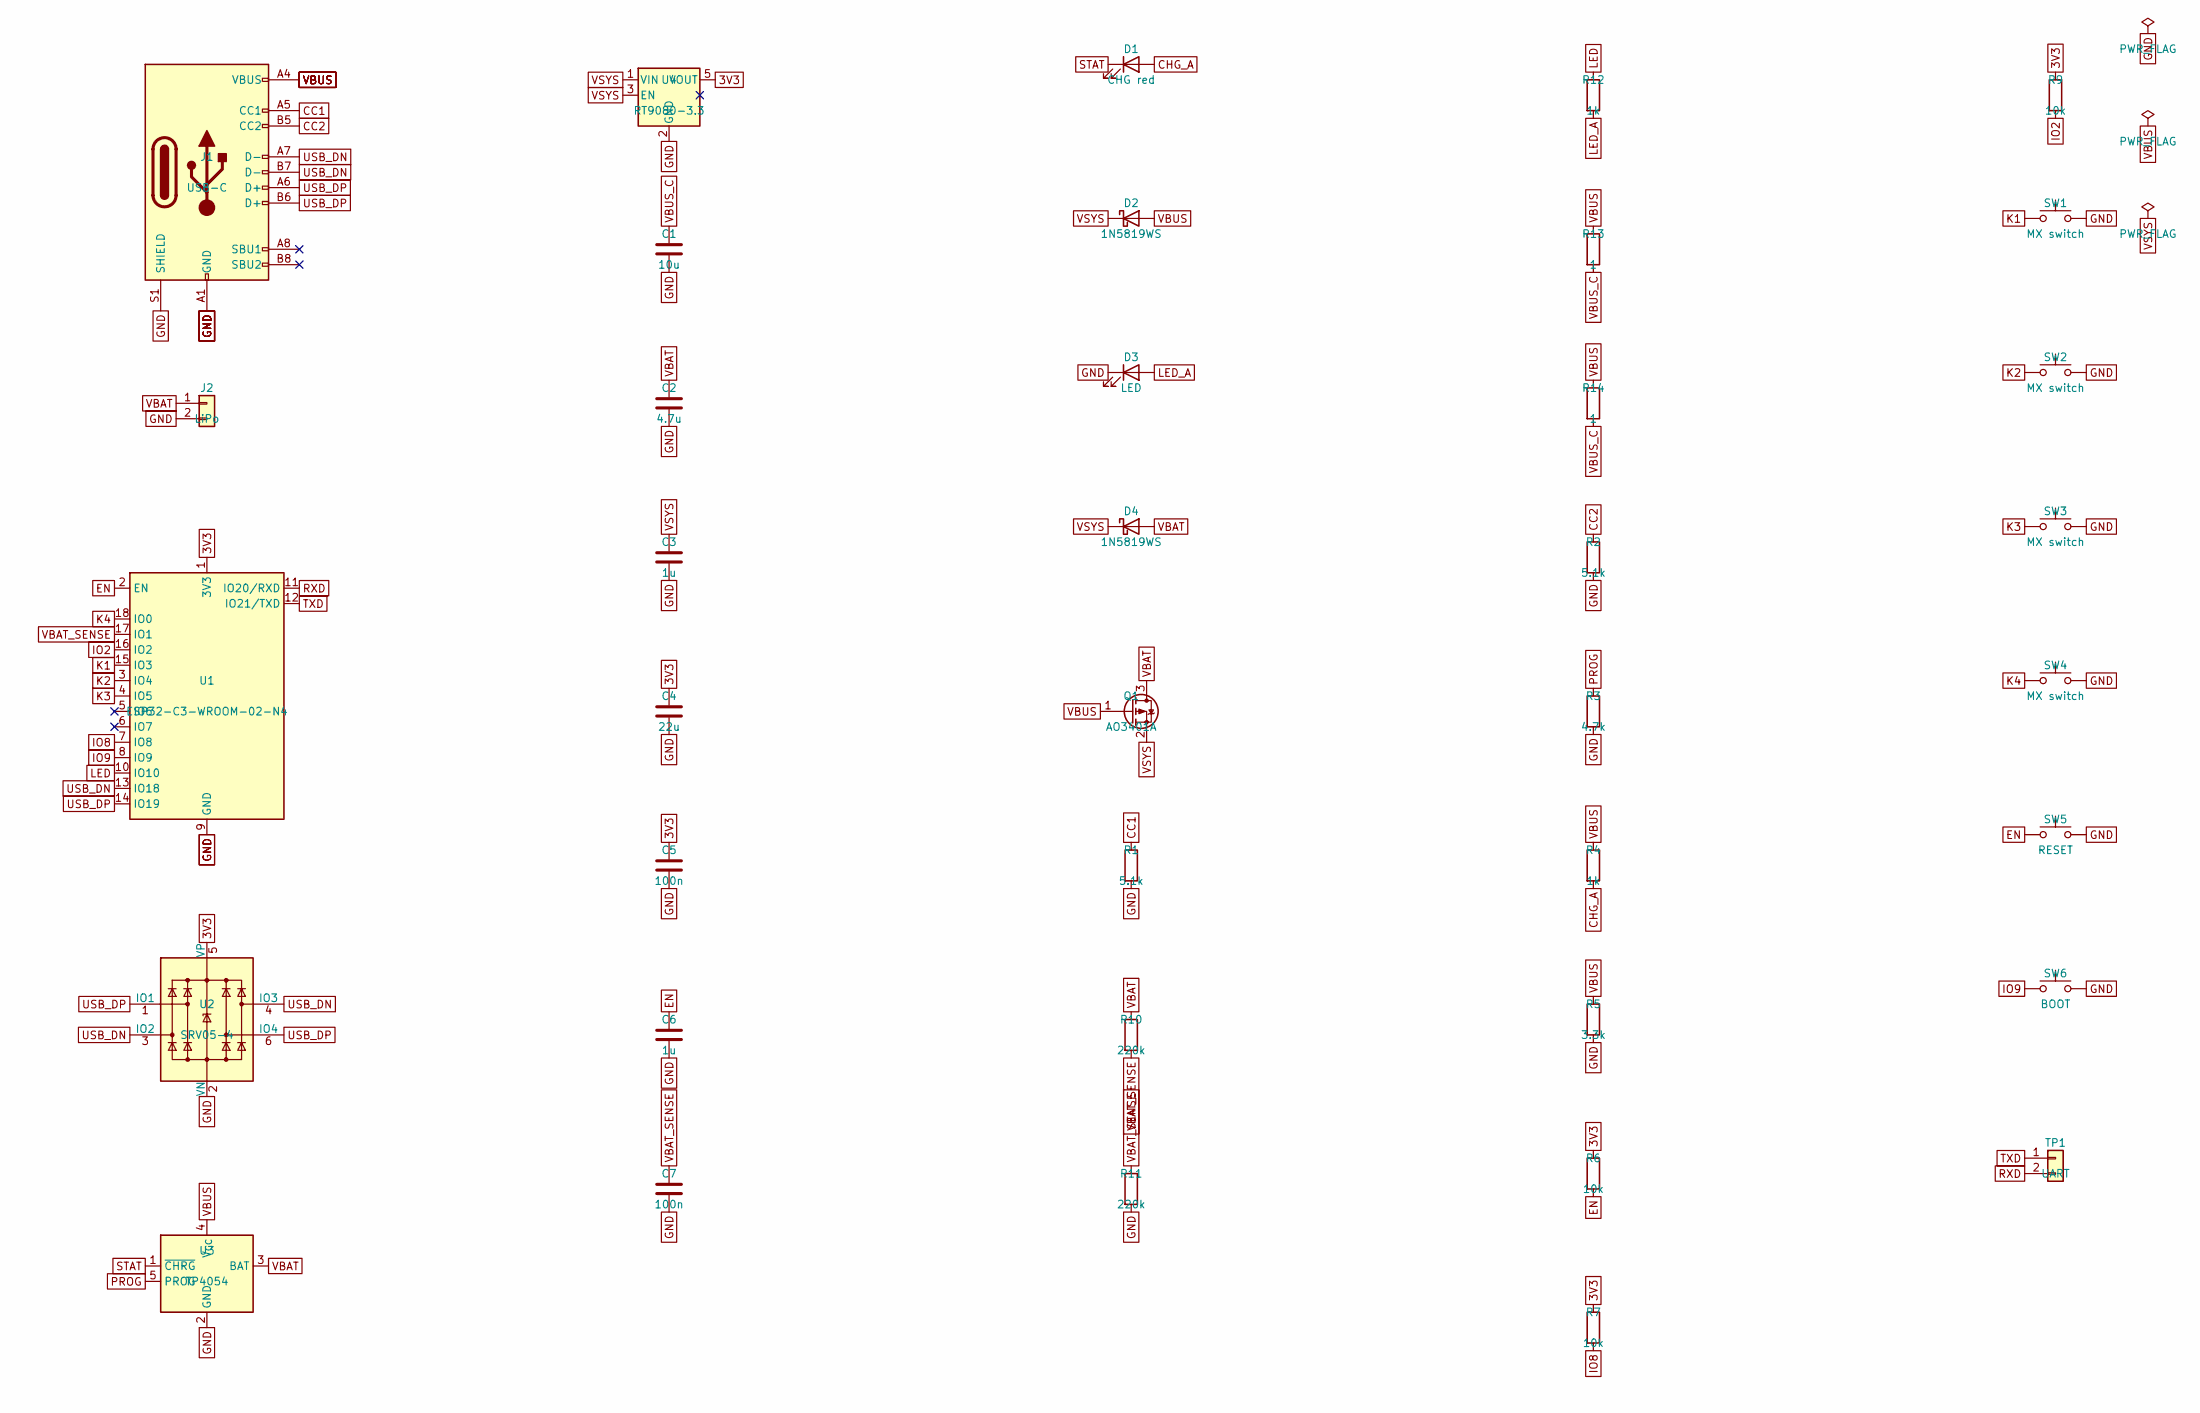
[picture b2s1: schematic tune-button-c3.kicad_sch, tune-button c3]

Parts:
C1: 10u; C_0805_2012Metric; LCSC C15850
C2: 4.7u; C_0603_1608Metric; LCSC C19666
C3, C6: 1u; C_0603_1608Metric; LCSC C15849
C4: 22u; C_0805_2012Metric; LCSC C45783
C5, C7: 100n; C_0603_1608Metric; LCSC C14663
D1: CHG red; LED_0805_2012Metric
D2, D4: 1N5819WS; D_SOD-323; MPN 1N5819WS; LCSC C191023
D3: LED; LED_0805_2012Metric
J1: USB-C; USB_C_Receptacle_HRO_TYPE-C-31-M-12; MPN HRO TYPE-C-31-M-12; LCSC C165948
J2: LiPo; JST_PH_S2B-PH-SM4-TB_1x02-1MP_P2.00mm_Horizontal; MPN JST S2B-PH-SM4-TB; LCSC C295747
Q1: AO3401A; SOT-23; MPN AO3401A; LCSC C15127
R1, R2: 5.1k; R_0603_1608Metric; LCSC C23186
R3: 4.7k; R_0603_1608Metric; LCSC C23162
R4, R12: 1k; R_0603_1608Metric; LCSC C21190
R5: 3.3k; R_0603_1608Metric; LCSC C22978
R6, R7, R9: 10k; R_0603_1608Metric; LCSC C25804
R10, R11: 220k; R_0603_1608Metric; LCSC C22961
R13, R14: 1; R_1206_3216Metric; LCSC C17928
SW1, SW2, SW3, SW4: MX switch; SW_Cherry_MX_1.00u_PCB; MPN Cherry MX (3 or 5 pin)
SW5: RESET; SW_Push_1P1T_XKB_TS-1187A; MPN XKB TS-1187A-B-A-B; LCSC C318884
SW6: BOOT; SW_Push_1P1T_XKB_TS-1187A; MPN XKB TS-1187A-B-A-B; LCSC C318884
TP1: UART; PinHeader_1x02_P2.54mm_Vertical
U1: ESP32-C3-WROOM-02-N4; ESP32-C3-WROOM-02; MPN ESP32-C3-WROOM-02-N4; LCSC C2934560
U2: SRV05-4; SOT-23-6; MPN SRV05-4-P-T7; LCSC C85364
U3: TP4054; SOT-23-5; MPN TP4054-42-SOT25R; LCSC C32574
U4: RT9080-3.3; SOT-23-5; MPN RT9080-33GJ5; LCSC C841192

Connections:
3V3: C4.1, C5.1, R6.1, R7.1, R9.1, U1.1 (3V3), U2.5 (VP), U4.5 (VOUT)
CC1: J1.A5 (CC1), R1.1
CC2: J1.B5 (CC2), R2.1
CHG_A: D1.2 (A), R4.2
EN: C6.1, R6.2, SW5.1, U1.2 (EN)
GND: C1.2, C2.2, C3.2, C4.2, C5.2, C6.2, C7.2, D3.1 (K), J1.A1 (GND), J1.A12 (GND), J1.B1 (GND), J1.B12 (GND), J1.S1 (SHIELD), J2.2, R1.2, R2.2, R3.2, R5.2, R11.2, SW1.2, SW2.2, SW3.2, SW4.2, SW5.2, SW6.2, U1.9 (GND), U1.19 (GND), U2.2 (VN), U3.2 (GND), U4.2 (GND)
IO2: R9.2, U1.16 (IO2)
IO8: R7.2, U1.7 (IO8)
IO9: SW6.1, U1.8 (IO9)
K1: SW1.1, U1.15 (IO3)
K2: SW2.1, U1.3 (IO4)
K3: SW3.1, U1.4 (IO5)
K4: SW4.1, U1.18 (IO0)
LED: R12.1, U1.10 (IO10)
LED_A: D3.2 (A), R12.2
PROG: R3.1, U3.5 (PROG)
RXD: TP1.2, U1.11 (IO20/RXD)
STAT: D1.1 (K), U3.1 (~CHRG)
TXD: TP1.1, U1.12 (IO21/TXD)
USB_DN: J1.A7 (D-), J1.B7 (D-), U1.13 (IO18), U2.3 (IO2), U2.4 (IO3)
USB_DP: J1.A6 (D+), J1.B6 (D+), U1.14 (IO19), U2.1 (IO1), U2.6 (IO4)
VBAT: C2.1, D4.2 (A), J2.1, Q1.3 (D), R10.1, U3.3 (BAT)
VBAT_SENSE: C7.1, R10.2, R11.1, U1.17 (IO1)
VBUS: D2.2 (A), J1.A4 (VBUS), J1.A9 (VBUS), J1.B4 (VBUS), J1.B9 (VBUS), Q1.1 (G), R4.1, R5.1, R13.1, R14.1, U3.4 (V_{CC})
VBUS_C: C1.1, R13.2, R14.2
VSYS: C3.1, D2.1 (K), D4.1 (K), Q1.2 (S), U4.1 (VIN), U4.3 (EN)

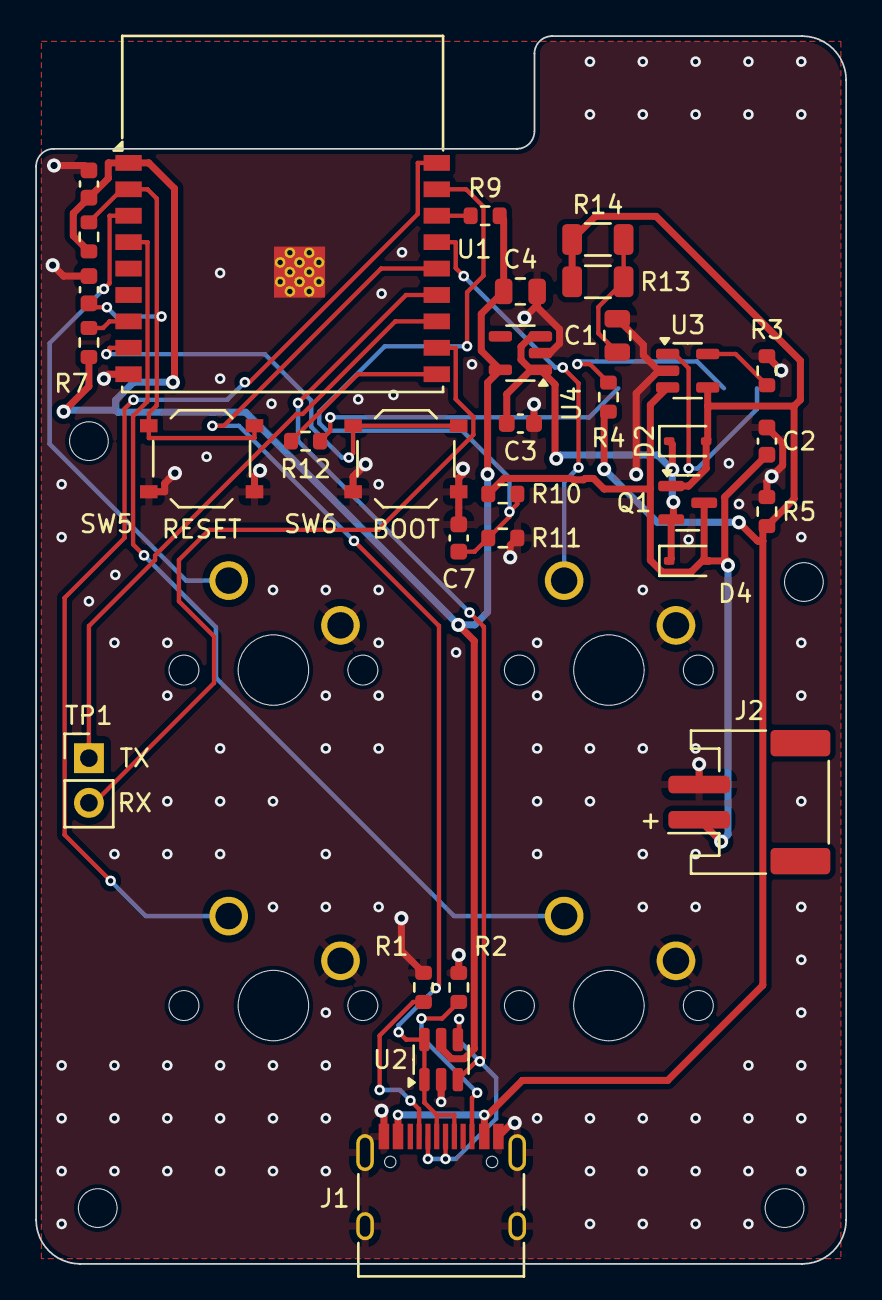
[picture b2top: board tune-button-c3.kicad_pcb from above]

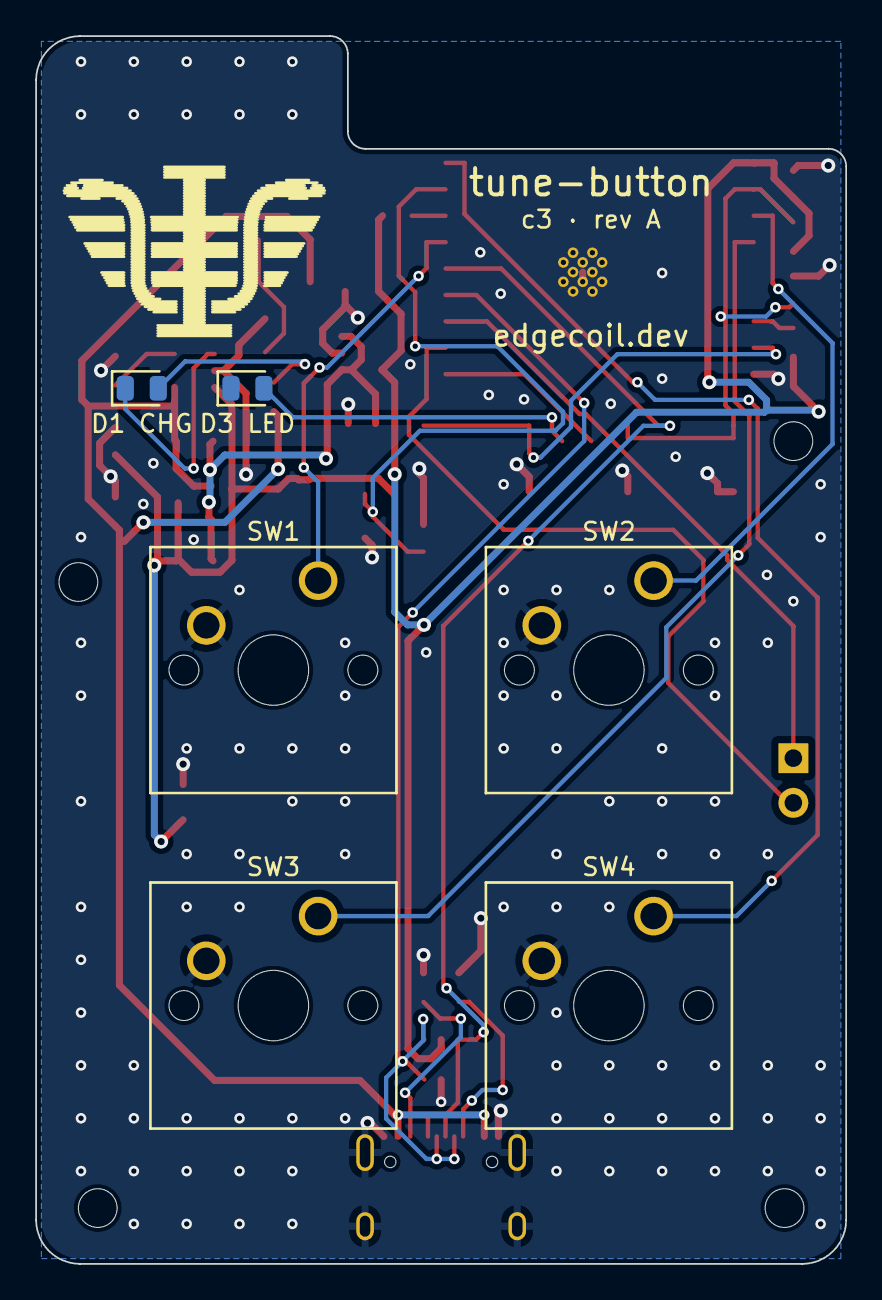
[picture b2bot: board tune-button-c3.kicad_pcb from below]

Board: 2 copper layers, 46.0 x 69.7 mm, 42 parts (6 on the bottom side), 26 nets.

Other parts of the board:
H1, H2, H3, H4: M2; MountingHole_2.2mm_M2
